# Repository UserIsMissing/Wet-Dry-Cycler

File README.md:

# Wet-Dry-Cycler
Capstone ECE 129

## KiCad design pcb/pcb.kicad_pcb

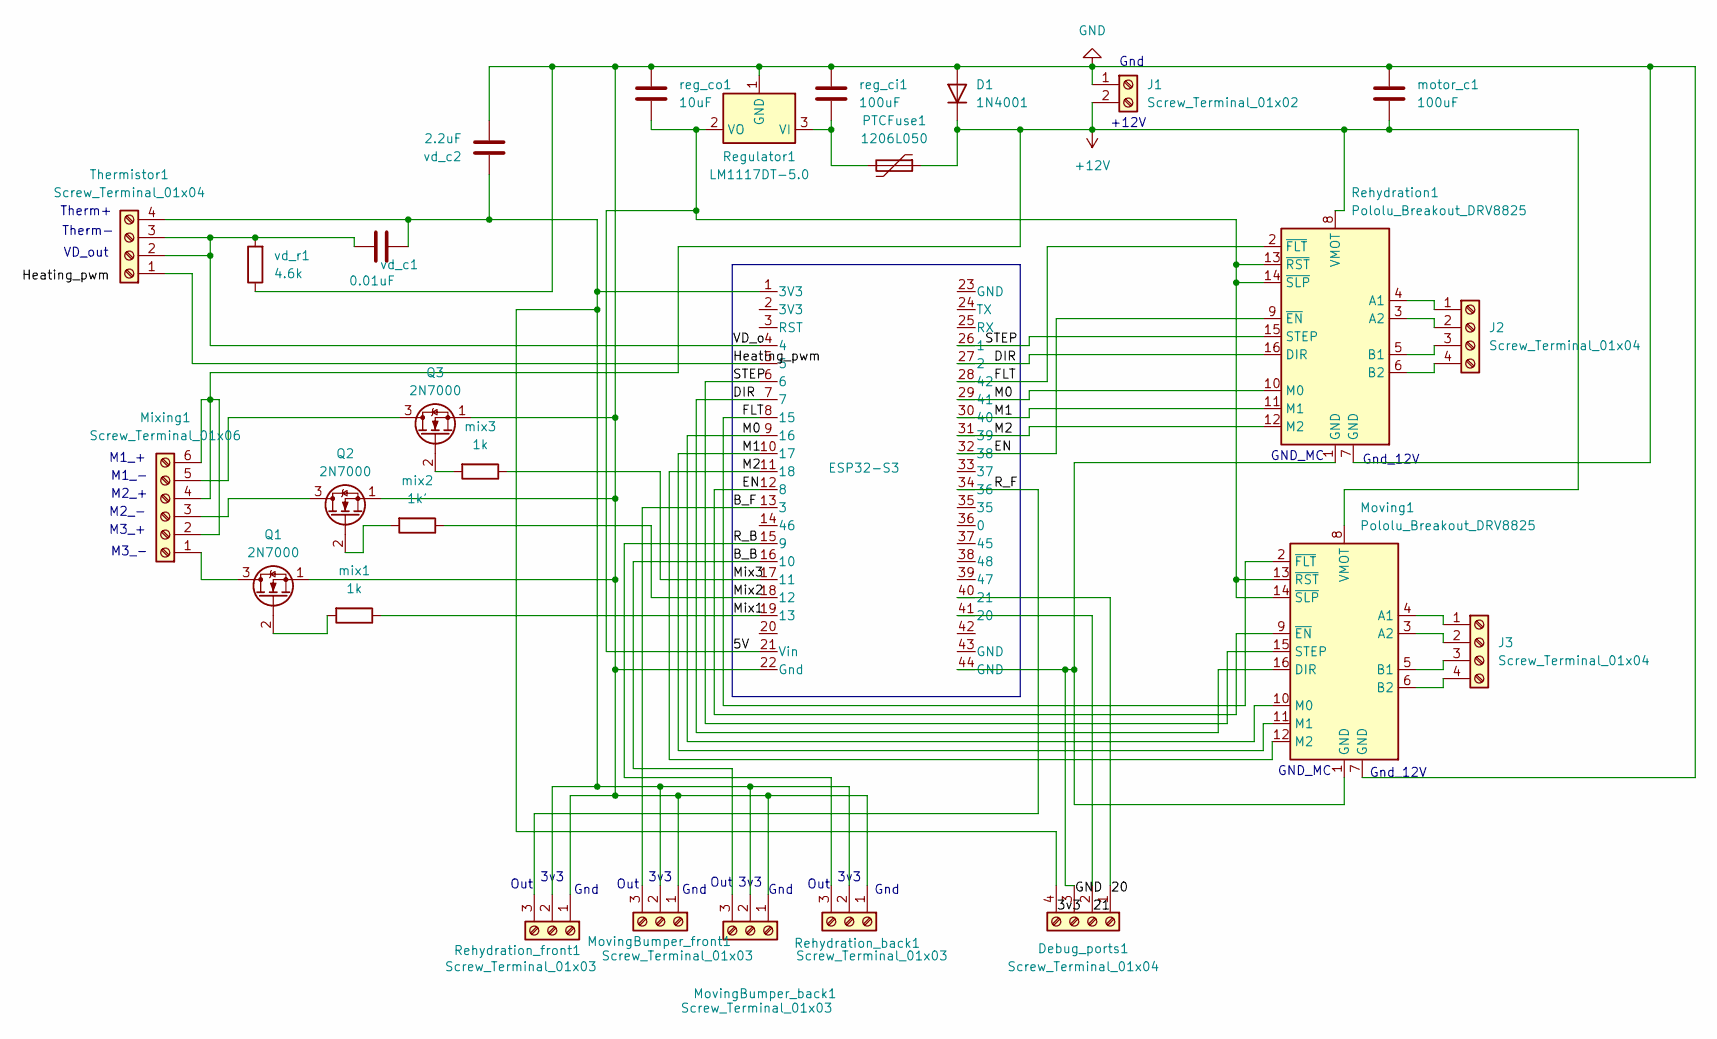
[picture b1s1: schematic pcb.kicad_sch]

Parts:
D1: 1N4001; D_DO-41_SOD81_P10.16mm_Horizontal
Debug_ports1: Screw_Terminal_01x04; TerminalBlock_MaiXu_MX126-5.0-04P_1x04_P5.00mm
ESP32-S3: ESP32_DevKitC_Header_Mount
J1: Screw_Terminal_01x02; TerminalBlock_MaiXu_MX126-5.0-02P_1x02_P5.00mm
J2, J3: Screw_Terminal_01x04; TerminalBlock_MaiXu_MX126-5.0-04P_1x04_P5.00mm
Mixing1: Screw_Terminal_01x06; TerminalBlock_MaiXu_MX126-5.0-06P_1x06_P5.00mm
Moving1: Pololu_Breakout_DRV8825; Pololu_Breakout-16_15.2x20.3mm
MovingBumper_back1: Screw_Terminal_01x03; TerminalBlock_MaiXu_MX126-5.0-03P_1x03_P5.00mm
MovingBumper_front1: Screw_Terminal_01x03; TerminalBlock_MaiXu_MX126-5.0-03P_1x03_P5.00mm
PTCFuse1: 1206L050; Fuse_1206_3216Metric_Pad1.42x1.75mm_HandSolder
Q1, Q2, Q3: 2N7000; TO-92_Inline
Regulator1: LM1117DT-5.0; TO-252-3_TabPin2
Rehydration1: Pololu_Breakout_DRV8825; Pololu_Breakout-16_15.2x20.3mm
Rehydration_back1: Screw_Terminal_01x03; TerminalBlock_MaiXu_MX126-5.0-03P_1x03_P5.00mm
Rehydration_front1: Screw_Terminal_01x03; TerminalBlock_MaiXu_MX126-5.0-03P_1x03_P5.00mm
Thermistor1: Screw_Terminal_01x04; TerminalBlock_MaiXu_MX126-5.0-04P_1x04_P5.00mm
mix1, mix3: 1k; R_Axial_DIN0207_L6.3mm_D2.5mm_P7.62mm_Horizontal
mix2: 1k'; R_Axial_DIN0207_L6.3mm_D2.5mm_P7.62mm_Horizontal
motor_c1: 100uF; CP_Radial_D6.3mm_P2.50mm
reg_ci1: 100uF; CP_Radial_D6.3mm_P2.50mm
reg_co1: 10uF; CP_Radial_D5.0mm_P2.50mm
vd_c1: 0.01uF; C_Disc_D3.0mm_W1.6mm_P2.50mm
vd_c2: 2.2uF; CP_Radial_D5.0mm_P2.50mm
vd_r1: 4.6k; R_Axial_DIN0207_L6.3mm_D2.5mm_P7.62mm_Horizontal

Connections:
+12V: D1.1 (K), J1.2, Mixing1.2, Mixing1.4, Mixing1.6, Moving1.8 (VMOT), PTCFuse1.1, Rehydration1.8 (VMOT), motor_c1.2
/5V: ESP32-S3.21 (Vin), Moving1.13 (~RST), Moving1.14 (~SLP), Regulator1.2 (VO), Rehydration1.13 (~RST), Rehydration1.14 (~SLP), reg_co1.2
/B_B: ESP32-S3.16 (10), MovingBumper_back1.3
/B_F: ESP32-S3.13 (3), MovingBumper_front1.3
/DIR: ESP32-S3.7, ESP32-S3.27 (2), Moving1.16 (DIR), Rehydration1.16 (DIR)
/EN: ESP32-S3.12 (8), ESP32-S3.32 (38), Moving1.9 (~EN), Rehydration1.9 (~EN)
/FLT: ESP32-S3.8 (15), ESP32-S3.28 (42), Moving1.2 (~FLT), Rehydration1.2 (~FLT)
/Heating_pwm: ESP32-S3.5, Thermistor1.1
/M0: ESP32-S3.9 (16), ESP32-S3.29 (41), Moving1.10 (M0), Rehydration1.10 (M0)
/M1: ESP32-S3.10 (17), ESP32-S3.30 (40), Moving1.11 (M1), Rehydration1.11 (M1)
/M2: ESP32-S3.11 (18), ESP32-S3.31 (39), Moving1.12 (M2), Rehydration1.12 (M2)
/Mix1: ESP32-S3.19 (13), mix1.1
/Mix2: ESP32-S3.18 (12), mix2.1
/Mix3: ESP32-S3.17 (11), mix3.1
/R_B: ESP32-S3.15 (9), Rehydration_back1.3
/R_F: ESP32-S3.34 (36), Rehydration_front1.3
/STEP: ESP32-S3.6, ESP32-S3.26 (1), Moving1.15 (STEP), Rehydration1.15 (STEP)
/VD_o: ESP32-S3.4, Thermistor1.2, Thermistor1.3, vd_c1.1, vd_r1.2
GND: D1.2 (A), ESP32-S3.22 (Gnd), J1.1, Moving1.7 (GND), MovingBumper_back1.1, MovingBumper_front1.1, Q1.1 (S), Q2.1 (S), Q3.1 (S), Regulator1.1 (GND), Rehydration1.7 (GND), Rehydration_back1.1, Rehydration_front1.1, motor_c1.1, reg_ci1.1, reg_co1.1, vd_c2.2, vd_r1.1
unnamed: Debug_ports1.1, ESP32-S3.40 (21)
unnamed: Debug_ports1.2, ESP32-S3.41 (20)
unnamed: Debug_ports1.3, ESP32-S3.44 (GND), Moving1.1 (GND), Rehydration1.1 (GND)
unnamed: Debug_ports1.4, ESP32-S3.1 (3V3), MovingBumper_back1.2, MovingBumper_front1.2, Rehydration_back1.2, Rehydration_front1.2, Thermistor1.4, vd_c1.2, vd_c2.1
unnamed: J2.1, Rehydration1.4 (A1)
unnamed: J2.2, Rehydration1.3 (A2)
unnamed: J2.3, Rehydration1.5 (B1)
unnamed: J2.4, Rehydration1.6 (B2)
unnamed: J3.1, Moving1.4 (A1)
unnamed: J3.2, Moving1.3 (A2)
unnamed: J3.3, Moving1.5 (B1)
unnamed: J3.4, Moving1.6 (B2)
unnamed: Mixing1.1, Q1.3 (D)
unnamed: Mixing1.3, Q2.3 (D)
unnamed: Mixing1.5, Q3.3 (D)
unnamed: Q1.2 (G), mix1.2
unnamed: Q2.2 (G), mix2.2
unnamed: Q3.2 (G), mix3.2
unnamed: PTCFuse1.2, Regulator1.3 (VI), reg_ci1.2

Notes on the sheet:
Out
3v3
M2_-
Gnd_12V
Gnd
Therm-
+12V
GND_MC
M1_+
M2_+
M1_-
M3_-
M3_+
Therm+
VD_out

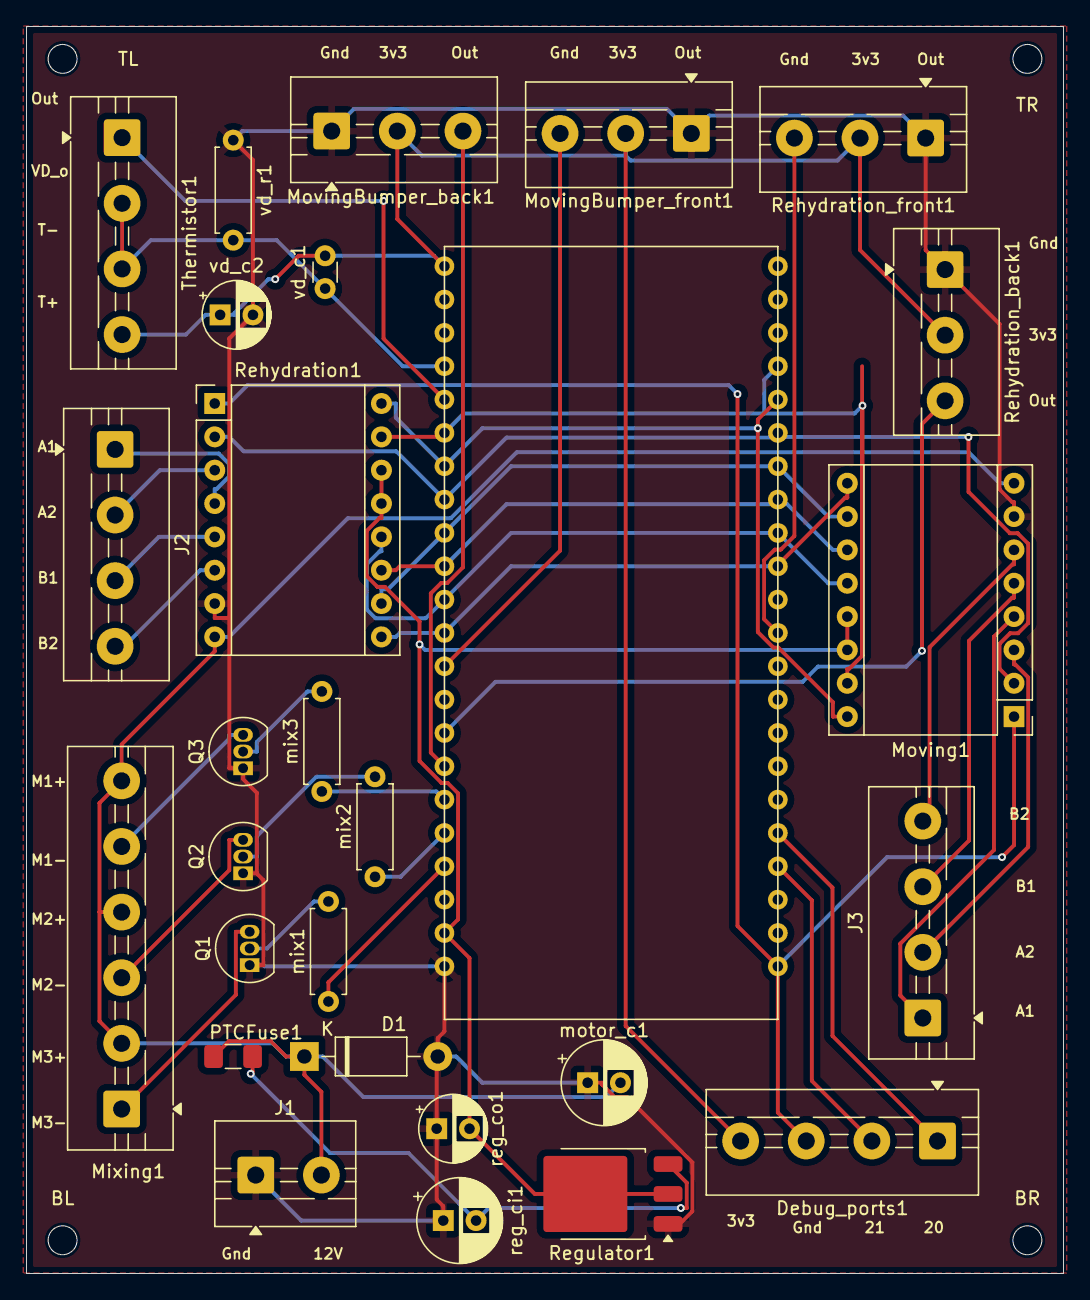
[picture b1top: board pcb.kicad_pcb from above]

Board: 2 copper layers, 79.0 x 95.0 mm, 32 parts (0 on the bottom side), 38 nets.

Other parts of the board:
BL: MountingHole_2.2mm_M2
BR: MountingHole_2.2mm_M2
TL: MountingHole_2.2mm_M2
TR: MountingHole_2.2mm_M2

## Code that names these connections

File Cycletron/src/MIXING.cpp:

/**
 * @file    MIXING.cpp
 * @brief   DC Motor control module using GPIO pins (Arduino/ESP32 compatible).
 *
 * Provides initialization and control functions for mixing motors.
 *
 * @author  Rafael Delwart
 * @date    25 Feb 2025 adapted for ESP 13 May 2025
 */

 #include <Arduino.h>
 #include "MIXING.h"
 

//  #define TESTING_MIXING

 // === CONFIG ===
 #define MIX1_GPIO 11
 #define MIX2_GPIO 12
 #define MIX3_GPIO 13  
 
 // Define motor GPIOs in an array for batch operations
 static const uint8_t motorPins[] = {MIX1_GPIO, MIX2_GPIO, MIX3_GPIO};
 static const int NUM_MOTORS = sizeof(motorPins) / sizeof(motorPins[0]);
 
 // === API IMPLEMENTATION ===
 
 /**
  * @brief Initializes all mixing motor GPIOs as OUTPUT and sets them LOW.
  */
 void MIXING_Init() {
   for (int i = 0; i < NUM_MOTORS; i++) {
     pinMode(motorPins[i], OUTPUT);
     digitalWrite(motorPins[i], LOW);  // Motors off by default
   }
   Serial.println("[MIXING] All motors initialized and set to OFF");
 }
 
 /**
  * @brief Turns ON the motor connected to the given GPIO pin.
  * @param pin GPIO pin number
  */
 void MIXING_Motor_OnPin(uint8_t pin) {
   digitalWrite(pin, HIGH);
 }
 
 /**
  * @brief Turns OFF the motor connected to the given GPIO pin.
  * @param pin GPIO pin number
  */
 void MIXING_Motor_OffPin(uint8_t pin) {
   digitalWrite(pin, LOW);
 }
 
 /**
  * @brief Turns ON all defined motors.
  */
 void MIXING_AllMotors_On() {
   for (int i = 0; i < NUM_MOTORS; i++) {
     digitalWrite(motorPins[i], HIGH);
   }
 }
 
 /**
  * @brief Turns OFF all defined motors.
  */
 void MIXING_AllMotors_Off() {
   for (int i = 0; i < NUM_MOTORS; i++) {
     digitalWrite(motorPins[i], LOW);
   }
 }

// === TEST LOOP ===
// This section is for testing the mixing motors.
#ifdef TESTING_MIXING

void setup() {
  Serial.begin(115200);
  MIXING_Init();
}

void loop() {
  // Step through each motor
  for (int i = 0; i < NUM_MOTORS; i++) {
    Serial.printf("[TEST] Turning ON motor %d (GPIO %d)\n", i + 1, motorPins[i]);
    MIXING_Motor_OnPin(motorPins[i]);
    delay(10000); // ON for 10 seconds

    Serial.printf("[TEST] Turning OFF motor %d (GPIO %d)\n", i + 1, motorPins[i]);
    MIXING_Motor_OffPin(motorPins[i]);
    delay(3000);  // OFF for 3 seconds
  }

  // All motors ON
  Serial.println("[TEST] Turning ALL motors ON");
  MIXING_AllMotors_On();
  delay(20000);

  // All motors OFF
  Serial.println("[TEST] Turning ALL motors OFF");
  MIXING_AllMotors_Off();
  delay(5000);
}

#endif // TESTING_MIXING

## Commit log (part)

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2025-01-23 Stepper Motor running at half steps using the ECE167 library for the STM32
2025-02-18 First Push. Created a project
2025-02-20 Fixing Heating Module
2025-02-25 Initial heating module finished, test still need to be made
2025-02-26 Adding Mixing Module
2025-02-27 Adding Pin details and renaming pins
2025-03-02 Update MIXING.c pin identifier
2025-03-02 Update HEATING.c pin identifier
2025-03-16 Cleaned Up Mixing Code, and Changed heating to work with voltage divider IC
2025-03-29 git cleanup
2025-04-09 testing stepper driver using pwms
2025-04-09 push gpio add pin3
2025-04-11 Updated DRV8825 Library to be universal and work with multiple motors, tested code and other small changes everything appears to work(still need to test fault line)
2025-04-15 REHYDRATION code added
2025-04-15 adding movement code
2025-04-15 adding MOVEMENT pins
2025-04-15 fixed pinouts
2025-04-16 MOVEMENT finished? ready to test
2025-04-16 movement updates
2025-04-16 MOVEMENT ready for testing
2025-04-17 cant printf
2025-04-17 FIXED GPIO PINS
2025-04-18 Movement Ready for actual Testing
2025-04-20 Added an enable pin to the DRV8825 code in order to stop current draw when the motor isnt moving. Added for DRV example coded aswell as the Movement library
2025-04-20 Changed the heating system to use the BETA method instead, far more reliable and accurate. Seems to work great!
2025-04-21 Created rehydration, added some starter code, add some code to calculate uL per step, not sure of the math still needs to be tested.
2025-04-21 Fixing uL to step calculations
2025-04-22 Changed Mode pins for rehydration, changed GPIO to match, and updated Rehydation math
2025-04-22 Enable pin working. going to add ISR now for bumpers
2025-04-23 Created ISR for movement bumpers. Just need to test
2025-04-23 fixed syntax. need to test ISR
2025-04-23 tiny changes to main
2025-04-23 small fixes
2025-04-23 changed syringe diameter
2025-04-23 Changed mixing/heating pins and updated some code
2025-04-23 Fixing merge issues and GPIO file problems
2025-04-23 corrected movement
2025-04-23 creating functional state machine. still need to test
2025-04-23 State machine ready to test
2025-04-24 fixed state machine? still working on ISR testing
2025-04-24 ISR WORKS! needed to add // Add manual fallback EXTI->FTSR |= GPIO_PIN_8; // Ensure falling edge is enabled to board.c
2025-04-25 isr works. fixing state machine. need to fix movement states (stepper modes)
2025-04-26 trying to fix movement
2025-04-26 print bumpers
2025-04-29 clean branch
2025-04-29 project setup
2025-04-29 basic frontend
2025-04-30 ESP setup in C
2025-04-30 Web server to esp communication works
2025-04-30 About to make changes for fixing switches, GPIO's interrupt pins
2025-04-30 Fixed front and back bumpers but now start button (ISR) crashes
2025-04-30 Two way communication works, reads GPIO4(ADC) and graphs it and writes to GPIO 2 to turn an LED on and off
2025-04-30 Cleaned up code, added comments and clearity
2025-04-30 Switching front end to react, adc graph doesnt work but just example code. Still needs to be cleaned up
2025-04-30 cleaning up
2025-04-30 cleaning up even more
2025-04-30 small changes
2025-04-30 Fixing startup and bat file for easy startup
2025-05-04 small change to ISR priority
2025-05-05 New branch hopefully fixs access problem
2025-05-05 Fix: remove submodule status from client and track as normal directory
2025-05-05 settings change? .json idk
2025-05-05 adding ESP32 to project main
2025-05-05 Fixing for mac and school wifi, readme has instructions to run main.c on mac
2025-05-06 fixing some stuff, adding to donna wifi
2025-05-06 Only updates on button press, added a function for GPIO communication. Also started using Bulma for buttons, and added more buttons
2025-05-06 Changing the front end and adding heating module into the C code
2025-05-07 fixing hosting issues
2025-05-07 lil push, calm thang
2025-05-07 fixing startups
2025-05-07 fix up of esp code, thing the app.js does not work to get information correctly
2025-05-07 fixing front and adding startup bat
2025-05-07 fixing buttons, adding bulma and fixing startup(hopefully)
2025-05-07 adding permament IP host,not just local host
2025-05-08 updating website
2025-05-08 Temp graph not working. Added Page tabs
2025-05-08 finished schematic of pcb, need to review it before routing
2025-05-08 push rest
2025-05-08 missed a wire, put more names for screw terminals
2025-05-08 fix power line
2025-05-08 new pcb file saved
2025-05-08 fix voltage divider
2025-05-08 fix motor controller input to 5V
2025-05-08 mixing controllers to 12V and add extra screw terminal for heating control
2025-05-08 changed names for moving bumper_start to rehydration back
2025-05-08 changed name for M0 to En, had 2 M0's
2025-05-08 finished labeling esp connections
2025-05-08 auto-routed pcb, might make smaller or a better layout
2025-05-09 finished layout
2025-05-09 edit names of blocks
2025-05-10 added text to pcb to show on gerber files
2025-05-12 forgot to pull, gonna force push this. I changed everything to through holes so we can soulder easier, added the board info onto pcb
2025-05-12 renamed screw holes
2025-05-12 push stl file
2025-05-12 push gcode for bambu
2025-05-12 updating startup scripts including bulma installer
2025-05-13 changing installer
2025-05-13 changing mac startup
2025-05-13 went backwards on installers
2025-05-13 edit minimum width, add copper plate
2025-05-13 made some good changes to the frontend on mac. (ignoring home PC changes)
2025-05-13 Now adding inputs and progress bars on the side
2025-05-13 added esp outputs next to tabs
2025-05-13 Front end looks ALOT better
2025-05-13 visually perfect. now changing button interplay and greying out
2025-05-14 adding state machine to esp to deal with the front end commands(still a lot of work to be done)
2025-05-14 Merging before adding server storage
2025-05-14 ported over STM code, still needs to be tested
2025-05-14 minor changes added rehydration init based on inputed parameters
2025-05-15 adding tests
2025-05-15 adding tests and matthews rerouted pcb
2025-05-15 gonna work on PC now
2025-05-15 small changes from PC
2025-05-15 updated extraction ready light indicator on website
2025-05-15 trying to create backend storage for recovery
2025-05-16 Front end works, just need to fix disconnecting issue
2025-05-16 fixing tests/ heating
2025-05-16 trying to get web hooks, sockets, and everything working before logg storage deals. still disconnects after seconds
2025-05-16 I think i got the UI close to where it was but now uses propper web hooks and sockets
2025-05-16 didnt change anything
2025-05-16 Changing esp to be webscoket instead of server
2025-05-16 tiny changes. and recovery json worked?
2025-05-16 small changes clean up
2025-05-16 pushing to fix
2025-05-16 temp sending
2025-05-16 a bunch of changes for server side stuff
2025-05-16 "Go" button works now
2025-05-16 ok, site looks very very very good. buttons look mostly good, backend front end and esp all talk to eachother. need to continue working on file saving. "recovery_state.json" works
2025-05-17 added slightly more recovery functionality. just need to add log data functionality
2025-05-17 git ignore esp_data.db
2025-05-17 more git ignore changes
2025-05-17 Just added "Log_Cycle.json"
2025-05-17 should open json in mac and windows
2025-05-17 reconnected timer shorter
2025-05-17 recovery_state/json now passes parameters set in the beginning. still need to add all buttons to recovery state
2025-05-17 adding interrupts for bumpers
2025-05-17 adding comments to rehydration isr
2025-05-18 Added a "Vial Setup State upon page load"
2025-05-19 pushing changes for campus
2025-05-19 going to add a heartbeat Every second in "IDLE" state
2025-05-20 added mixing test
2025-05-20 fixing mixing test and deleting duplicate main/temp test
2025-05-21 Added some recovery stuff? Pushing to work from home
2025-05-21 FINALLY "Set Parameter" numbers are persistent across reloads and end cycle
2025-05-21 Logging and recovery files are REALLY great. Need to fix certain buttons upon reload
2025-05-21 Front and backend are great. double check with team. Only need to setup esp32 recovery files and passing parameters back and forth with rafael
2025-05-21 updating git ignore
2025-05-21 add other states for a FSM (heating, mixing rehydration) and send to server for recovery json file
2025-05-21 changing running to mixing rehydration ect
2025-05-21 recovery files sent to esp looks fixed.
2025-05-21 fixing parameters
2025-05-21 adding state flags and progress flags
2025-05-21 cycle end logic added
2025-05-21 lil change
2025-05-22 recovery and syringe refill logic
2025-05-22 clearing up all git
2025-05-22 heartbeat fixed
2025-05-23 cleaning up C and main code
2025-05-23 fixing pause button to keep timing
2025-05-23 adding vial setup state
2025-05-23 idk why but esp wont accept set parameters. also need to fix esp recovery. doesnt have current state because of ESP state machine not running
2025-05-23 pull this. normalizing packet
2025-05-23 changing parameters read to int
2025-05-23 fixed server.js so it no longer causes esp to disconnect on set parameters
2025-05-23 cycle progress working great. esp doesnt disconnect. Next, front end needs to reset on ended cycle
2025-05-23 looks like the website is in a good position and very close to done
2025-05-23 Just made small UI changes. Next need to get ESP_Recovery working
2025-05-24 Getting closer to esp recovery. it still disconnects and reconnects but is able to being it's cycles. however doesnt retain memory of last state on restart
2025-05-27 changing test for drv8825
2025-05-28 bumper update
2025-05-29 just changing final report latex stuff
2025-05-29 Making "End Cycle" always go to Vial setup
2025-06-02 I think i got esp recovery working. Resumes on reset, doesnt disconnect, need to test tomorrow
2025-06-03 changes to make it work almost fully need recovery and syringe refill logic
2025-06-03 fixing startup scripts
2025-06-03 trying to fix mac startup server command
2025-06-03 Server runs correctly on mac now. Also, esp32 status STAYS CONNECTED
2025-06-03 removed all test files
2025-06-03 Reset Recovery Data also deletes esp recovery now
2025-06-03 back to sm that works
2025-06-03 Switched to Raf's esp code from HardWare_StateMachine commit "back to sm that works"
2025-06-03 adding more webscoket prints to help create recovery files
2025-06-03 Raf - adding more webscoket prints to help create recovery files
2025-06-03 ESP recovery WORKS
2025-06-04 extraction and vial setup changes
2025-06-04 Updating changes before pushing to main
2025-06-04 new ESP top main branch(cole still needs to merge)
2025-06-04 Merging Cole And Rafael Branches to main
2025-06-04 changing windows websocket
2025-06-04 now server works on mac and PC
2025-06-04 fixing accidentaly push to main and rechanging the websocket so that it works on mac and windows
2025-06-04 Reset esp from frontend
2025-06-04 added breaks for debugging and updated bat for dependencies
2025-06-05 tiny change to reset recovery?
2025-06-05 Old code for COMPARE TEST
2025-06-05 idk copilot said to try this
2025-06-05 Works on PC - removed ESP_RECOVERY from server.js. also changed main.cpp to work without box (no movement) (No disconnect)
2025-06-05 4REAL - Works on PC - removed ESP_RECOVERY from server.js. also changed main.cpp to work without box (no movement) (No disconnect)
2025-06-06 server still works on PC. Changed to SQLite Database Storage for ESP Recovery
2025-06-06 ESP RECOVERY WORKS ON PC - Replaced File I/O with SQLite Database
2025-06-08 cleaning up state machine and fixing minor bugs, also syringe refill works still needs to be refined
2025-06-08 Small UI Changes
2025-06-08 small UI change, adding IP to front end
2025-06-08 adding extract ready and cleaning up
2025-06-08 working on extraction ready
2025-06-08 quality of life visuals. extraction ready is ready
2025-06-26 Add error hadnling and cleanup
2025-06-26 added system state display
2025-06-26 Added System Errors to front end
2025-07-03 Rehydration Test 2 for syringe calibration
2025-07-04 fixed syringe progress to ready or not, parameters allow 0 to be typed, heating in minutes
